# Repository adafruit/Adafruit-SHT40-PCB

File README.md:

## Adafruit SHT40, SHT41, and SHT45 Temperature & Humidity Sensor PCBs

<a href="http://www.adafruit.com/products/4885"><br/>
Click here to purchase the SHT40 from the Adafruit shop</a>

<a href="http://www.adafruit.com/products/5776"><br/>
Click here to purchase the SHT41 from the Adafruit shop</a>

<a href="http://www.adafruit.com/products/5665"><br/>
Click here to purchase the SHT45 from the Adafruit shop</a>

PCB files for the Adafruit SHT40, SHT41, and SHT45 Temperature & Humidity Sensors. 

Format is EagleCAD schematic and board layout
* https://www.adafruit.com/product/4885
* https://www.adafruit.com/product/5665
* https://www.adafruit.com/product/5776

### Description

Sensirion Temperature/Humidity sensors are some of the finest & highest-accuracy devices you can get. And finally, we have some that have a true I2C interface for easy reading. The SHT40, SHT41, and SHT45 sensors are the fourth generation (started at the SHT10 and worked its way up to the top!).

The SHT40 has an excellent ±1.8% typical relative humidity accuracy from 25 to 75% and ±0.2 °C typical accuracy from 0 to 75 °C.

The SHT41 has an excellent ±1.8% typical relative humidity accuracy from 25 to 75% and ±0.2 °C typical accuracy from 0 to 75 °C.

The SHT45 has an even more excellent ±1% typical relative humidity accuracy from 25 to 75% and ±0.1 °C typical accuracy from 0 to 75 °C.

Other than these differences in relative humidity and temperature accuracy, there is no discernible difference between these two chips. The I2C addresses and code are identical for both. So, how do you know which one you have? The text on the board indicates which breakout you have.

Unlike some earlier SHT sensors, this sensor has a true I2C interface for easy interfacing with only two wires (plus power and ground!). Thanks to the voltage regulator and level shifting circuitry we've included on the breakout It is also is 3V or 5V compliant, so you can power and communicate with it using any microcontroller or microcomputer.

Such a lovely chip - so we spun up a breakout board with the SHT4x and some supporting circuitry such as pullup resistors and capacitors. To make things even easier, we've included SparkFun Qwiic compatible STEMMA QT connectors for the I2C bus so you don't even need to solder! QT Cable is not included, but we have a variety in the shop.

If you prefer working on a breadboard, each order comes with one fully assembled and tested PCB breakout and a small piece of header. You'll need to solder the header onto the PCB, but it's fairly easy and takes only a few minutes even for a beginner.

We've written both Arduino and CircuitPython/Python library code for this chip, so you can use it with just about any microcontroller or single-board computer like Raspberry Pi.

### License

Adafruit invests time and resources providing this open source design, please support Adafruit and open-source hardware by purchasing products from [Adafruit](https://www.adafruit.com)!

Designed by Limor Fried/Ladyada for Adafruit Industries.

Creative Commons Attribution/Share-Alike, all text above must be included in any redistribution. 
See license.txt for additional details.

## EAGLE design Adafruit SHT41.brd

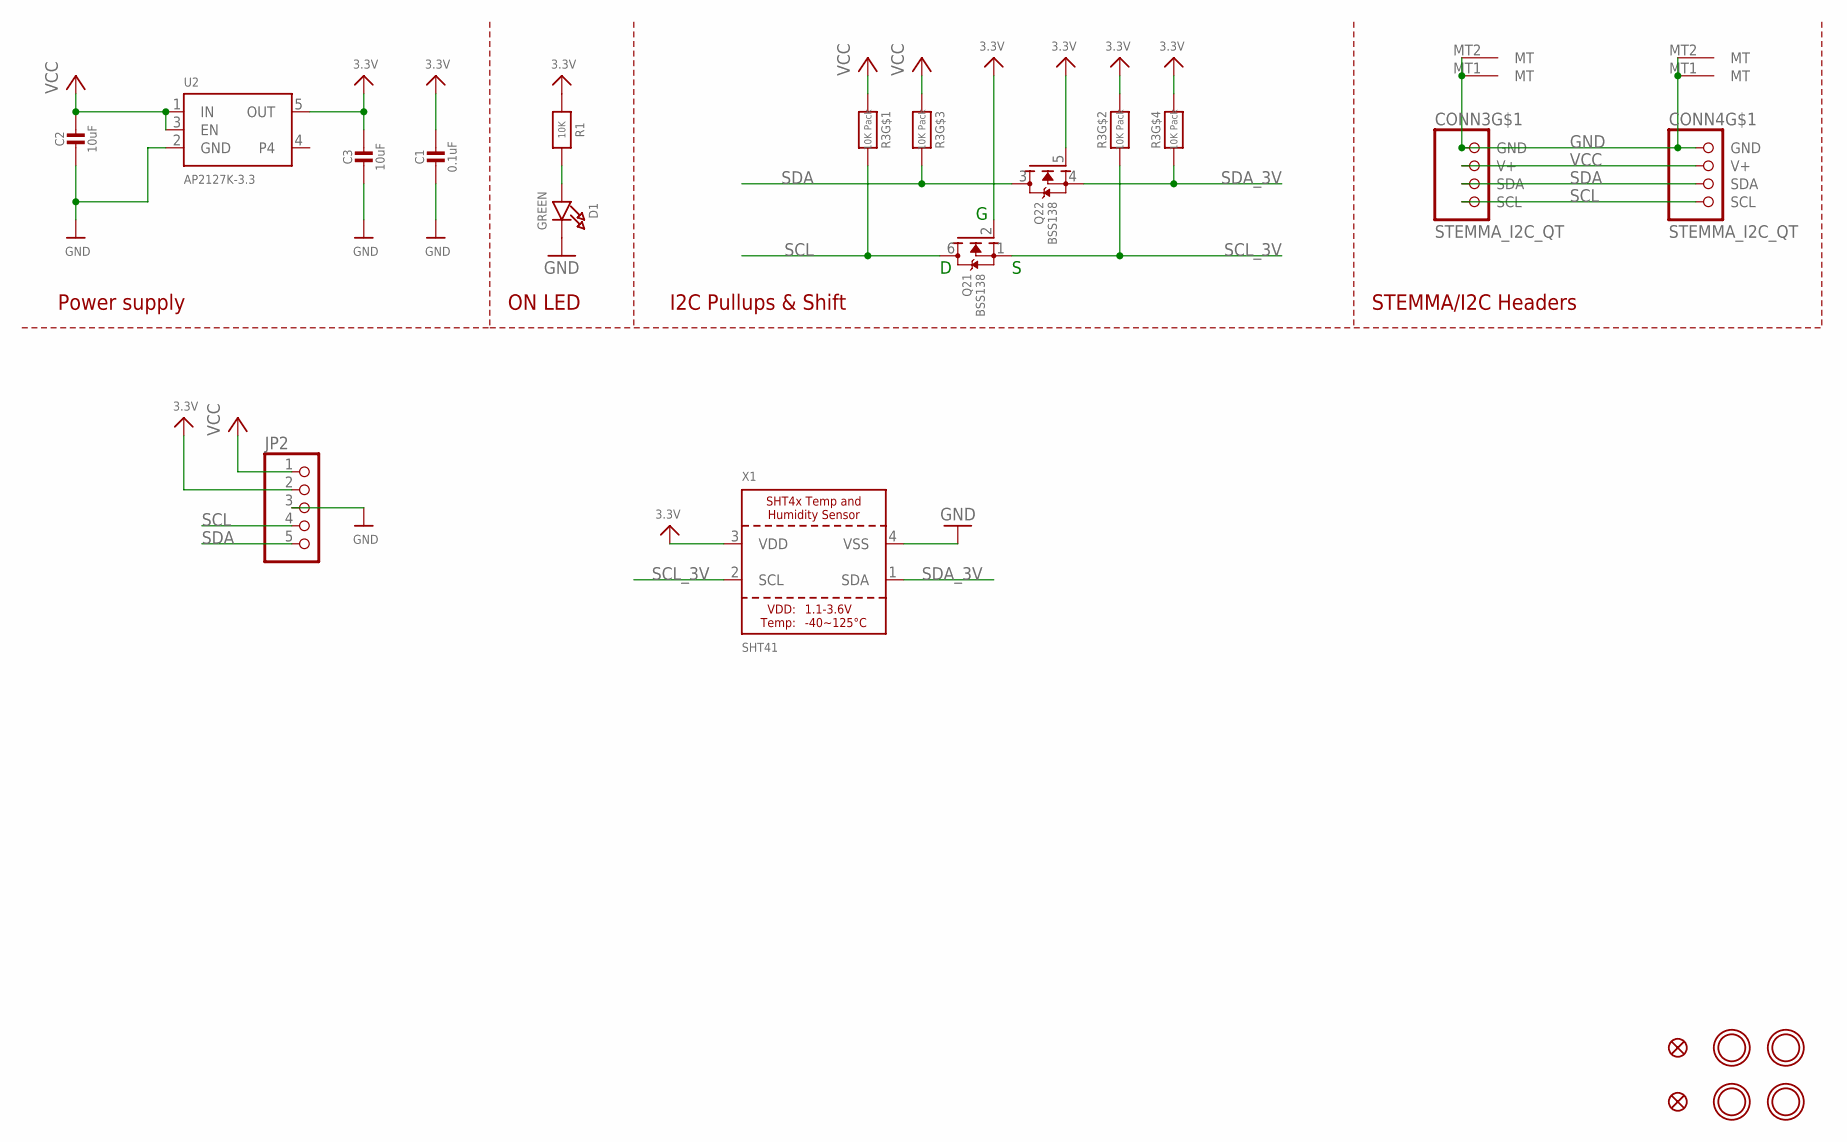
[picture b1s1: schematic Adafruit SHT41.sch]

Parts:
C1: 0.1uF; 0603-NO
C2, C3: 10uF; 0805-NO
CONN3, CONN4: STEMMA_I2C_QT; JST_SH4
D1: GREEN; CHIPLED_0603_NOOUTLINE
FID3, FID4: FIDUCIAL_1MM
JP2: HEADER-1X570MIL; 1X05_ROUND_70
Q2: BSS138; SOT363
R1: 10K; 0603-NO
R3: 10K Pack; RESPACK_4X0603
U2: AP2127K-3.3; SOT23-5
U$1, U$17, U$19, U$21: MOUNTINGHOLE2.5; MOUNTINGHOLE_2.5_PLATED
X1: SHT41; SHT4X

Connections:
3.3V: C1.1, C3.1, JP2.2, Q2.2 (G), Q2.5 (G), R1.1, R3.2 (1), R3.4 (1), U2.5 (OUT), X1.3 (VDD)
GND: C1.2, C2.2, C3.2, CONN3.1 (GND), CONN3.MT1 (MT), CONN3.MT2 (MT), CONN4.1 (GND), CONN4.MT1 (MT), CONN4.MT2 (MT), D1.C, JP2.3, U2.2 (GND), X1.4 (VSS)
unnamed: D1.A, R1.2
SCL: CONN3.4 (SCL), CONN4.4 (SCL), JP2.4, Q2.6 (D), R3.8 (2)
SCL_3V: Q2.1 (S), R3.7 (2), X1.2 (SCL)
SDA: CONN3.3 (SDA), CONN4.3 (SDA), JP2.5, Q2.3 (D), R3.6 (2)
SDA_3V: Q2.4 (S), R3.5 (2), X1.1 (SDA)
VCC: C2.1, CONN3.2 (V+), CONN4.2 (V+), JP2.1, R3.1, R3.3 (1), U2.1 (IN), U2.3 (EN)

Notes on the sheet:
I2C Pullups & Shift
STEMMA/I2C Headers
ON LED
Power supply

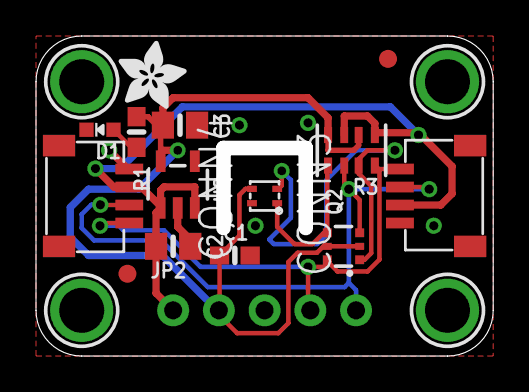
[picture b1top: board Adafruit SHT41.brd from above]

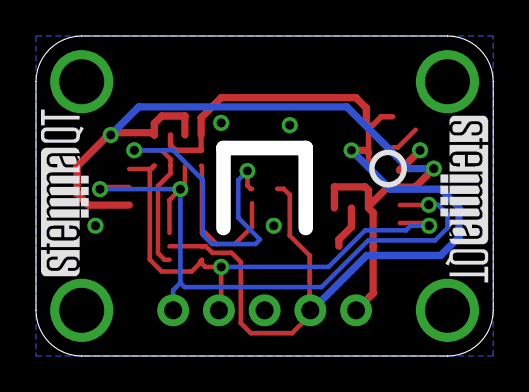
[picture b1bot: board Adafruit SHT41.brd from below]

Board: 2 copper layers, 24.6 x 17.0 mm, 35 parts (8 on the bottom side), 8 nets.

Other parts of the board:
PLABEL0: PLABEL0
PLABEL1: PLABEL1
PLABEL2: PLABEL2
PLABEL3: PLABEL3
PLABEL4: PLABEL4
PLABEL7: PLABEL7
PLABEL8: PLABEL8
PLABEL9: PLABEL9
PLABEL10: PLABEL10
PLABEL11: PLABEL11
PLABEL12: PLABEL12
PLABEL13: PLABEL13
PLABEL14: PLABEL14
U$22: ADAFRUIT_3.5MM
U$25: PCBFEAT-REV-040
U$30, U$31: STEMMAQT

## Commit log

2021-02-03 Adding board files.
2023-01-13 Add new board files.
2023-01-13 Update for SHT45
2023-07-06 Add board files.
2023-07-06 Add asset.
2023-07-06 Add SHT41.

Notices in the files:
parts and their libraries:
microbuilder: This work is placed in the public domain, and may be freely used for commercial and non-commercial work with the following conditions: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
